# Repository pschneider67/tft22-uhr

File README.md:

# Platine KiCad Projekt - tft22-uhr
Eine kleine Uhr mit dem ESP8266 D1 mini Modul.

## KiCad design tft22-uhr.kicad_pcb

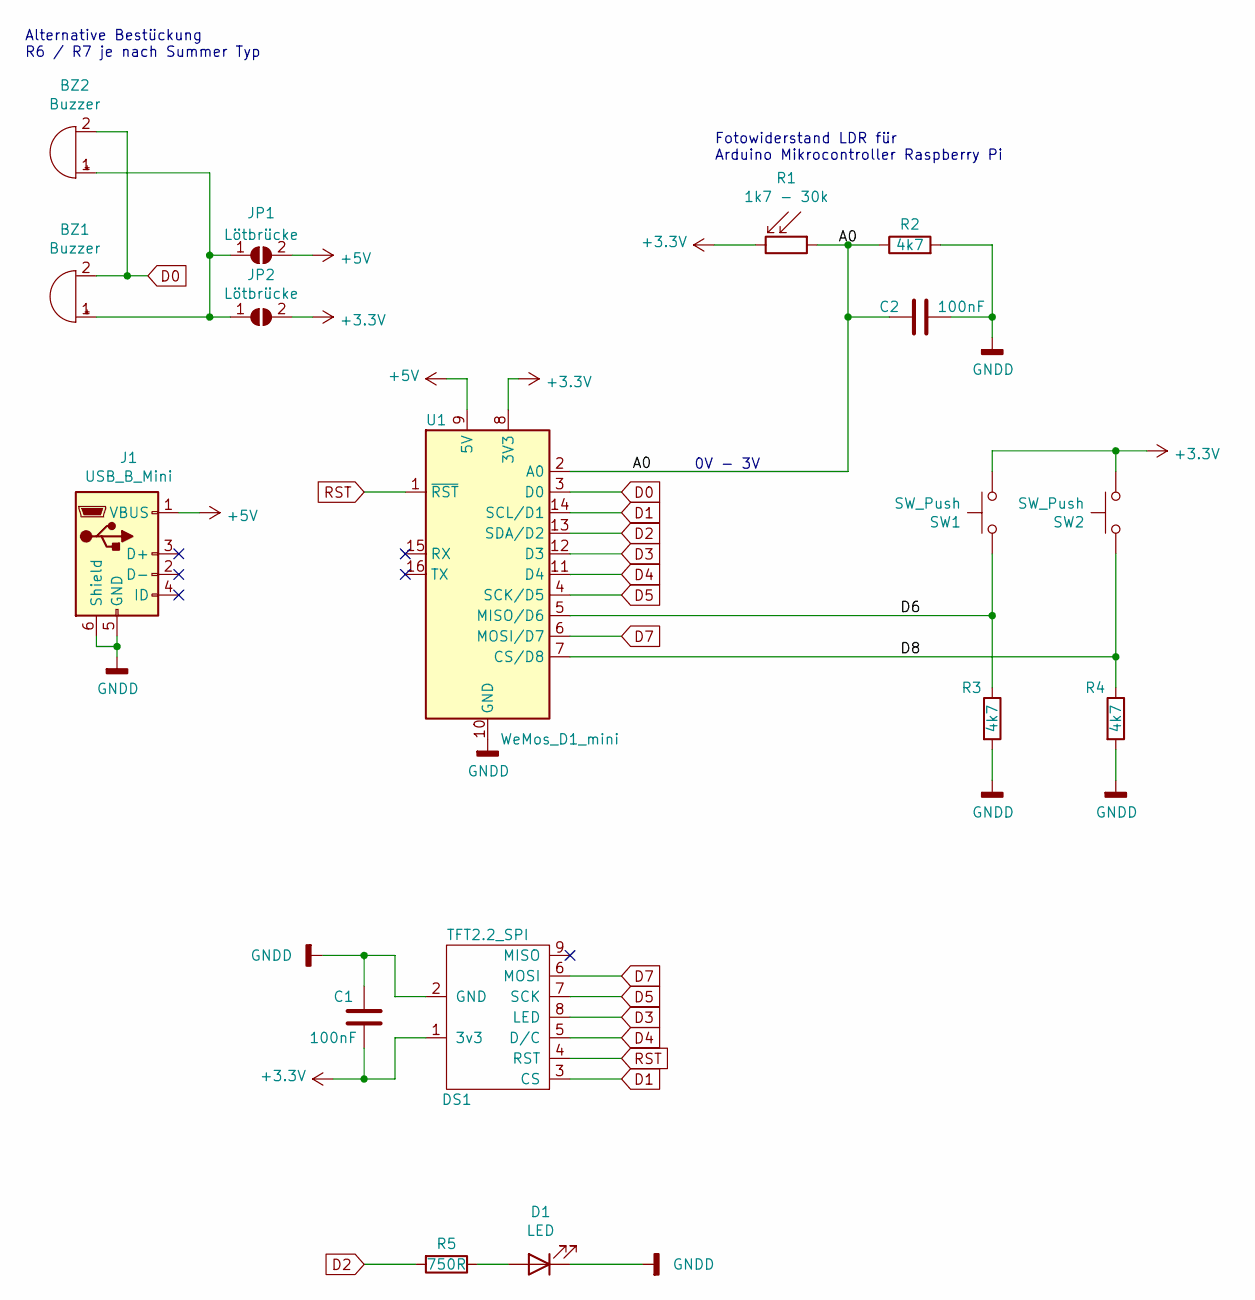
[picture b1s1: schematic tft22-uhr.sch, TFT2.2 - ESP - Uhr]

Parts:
BZ1: Buzzer; Buzzer_12x9.5RM7.6
BZ2: Buzzer; Buzzer_9x5RM5
C1, C2: 100nF; C_1206_3216Metric_Pad1.42x1.75mm_HandSolder
D1: LED; LED_D3.0mm
DS1: TFT2.2_SPI
J1: USB_B_Mini; USB_Mini-B_Lumberg_2486_01_Horizontal
JP1, JP2: Lötbrücke; SolderJumper-2_P1.3mm_Open_RoundedPad1.0x1.5mm
R1: 1k7 - 30k; R_Axial_DIN0207_L6.3mm_D2.5mm_P5.08mm_Vertical
R2, R3, R4: 4k7; R_1206_3216Metric_Pad1.42x1.75mm_HandSolder
R5: 750R; R_1206_3216Metric_Pad1.42x1.75mm_HandSolder
SW1, SW2: SW_Push; Taster_6x6x8_stehend
U1: WeMos_D1_mini; WEMOS_D1_mini_light

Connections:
+3V3: C1.2, DS1.1 (3v3), JP2.2 (B), R1.2, SW1.2, SW2.2, U1.8 (3V3)
+5V: J1.1 (VBUS), JP1.2 (B), U1.9 (5V)
/A0: C2.2, R1.1, R2.1, U1.2 (A0)
/D6: R3.1, SW1.1, U1.5 (MISO/D6)
/D8: R4.1, SW2.1, U1.7 (CS/D8)
D0: BZ1.2 (+), BZ2.2 (+), U1.3 (D0)
D1: DS1.3 (CS), U1.14 (SCL/D1)
D2: R5.2, U1.13 (SDA/D2)
D3: DS1.8 (LED), U1.12 (D3)
D4: DS1.5 (D/C), U1.11 (D4)
D5: DS1.7 (SCK), U1.4 (SCK/D5)
D7: DS1.6 (MOSI), U1.6 (MOSI/D7)
GNDD: C1.1, C2.1, D1.1 (K), DS1.2 (GND), J1.5 (GND), J1.6 (Shield), R2.2, R3.2, R4.2, U1.10 (GND)
unnamed: BZ1.1 (-), BZ2.1 (-), JP1.1 (A), JP2.1 (A)
unnamed: D1.2 (A), R5.1
RST: DS1.4 (RST), U1.1 (~RST)

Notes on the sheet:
Fotowiderstand LDR für Arduino Mikrocontroller Raspberry Pi
Alternative Bestückung R6 / R7 je nach Summer Typ
0V - 3V

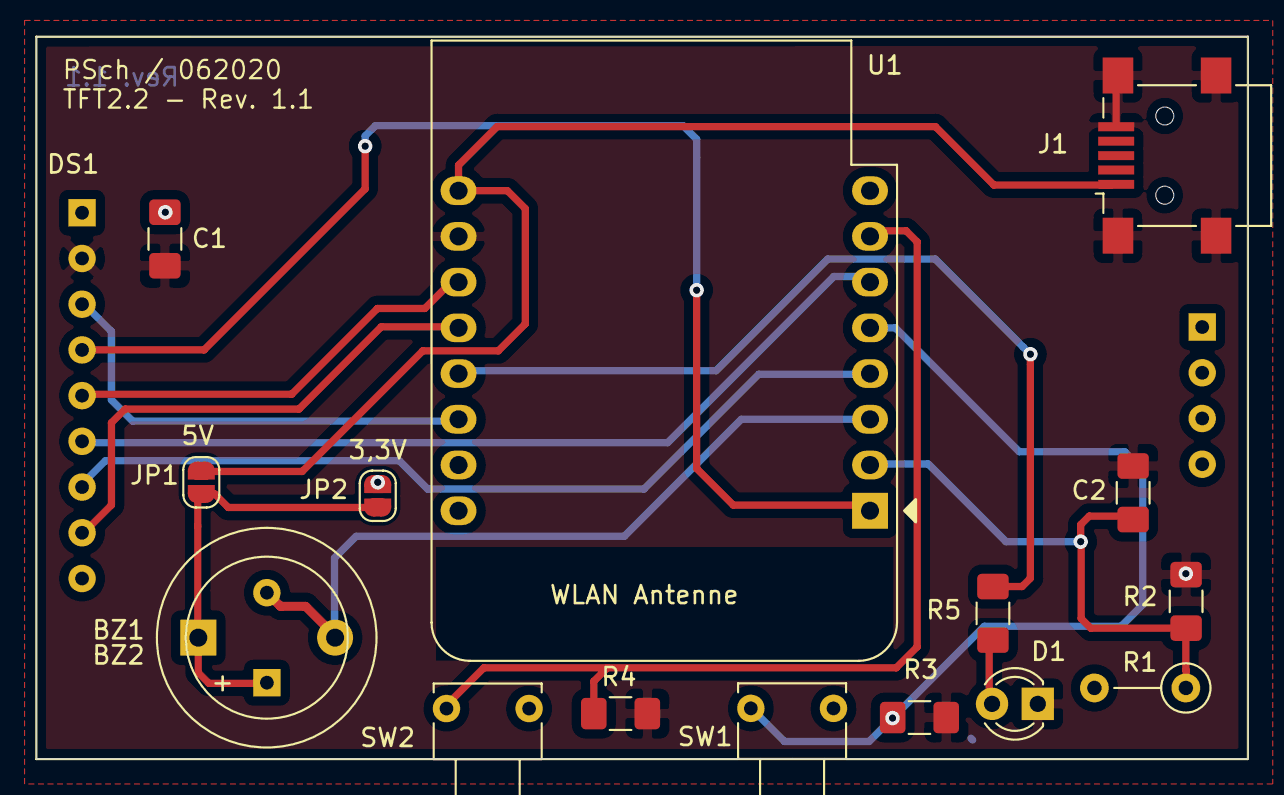
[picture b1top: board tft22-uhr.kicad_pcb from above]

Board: 2 copper layers, 67.3 x 40.1 mm, 17 parts (0 on the bottom side), 16 nets.

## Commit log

2021-11-05 start tft22-uhr
